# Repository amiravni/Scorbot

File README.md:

This is my work of building a Scorbot ER-V Controller with an arduino MEGA and drivers.

The project description is here: http://whatimade.today/geekcon-xii-scorbot-learns-to-draw/

Files and Folders consist of:

scorbotCOMcontrol - Most updated code, can get 6 encoder values and moves towards them

python - Python code for drawing images with scorbot

files - Some modified files to use with the python code

Eagle - Arduino mega shield design for scorbot

scorbotShieldTest - Shield Test...

Pins - Scorbot 50 Pins Data

ER3-Manual - Scorbot Manual

scorbotOldTestCode - My early work on scorbot, described here: http://www.whatimade.today/my-name-is-scorbot/

* Encoder_Scorbot - CPP code for encoders, taken and modified from  https://github.com/frodofski/Encoder_Polling_V2

* ScorbotCmd - The final code for controlling the Scorbot (Under Construction)

* ScorbotTest - Test code for Motors, Encoders and MicroSwitches

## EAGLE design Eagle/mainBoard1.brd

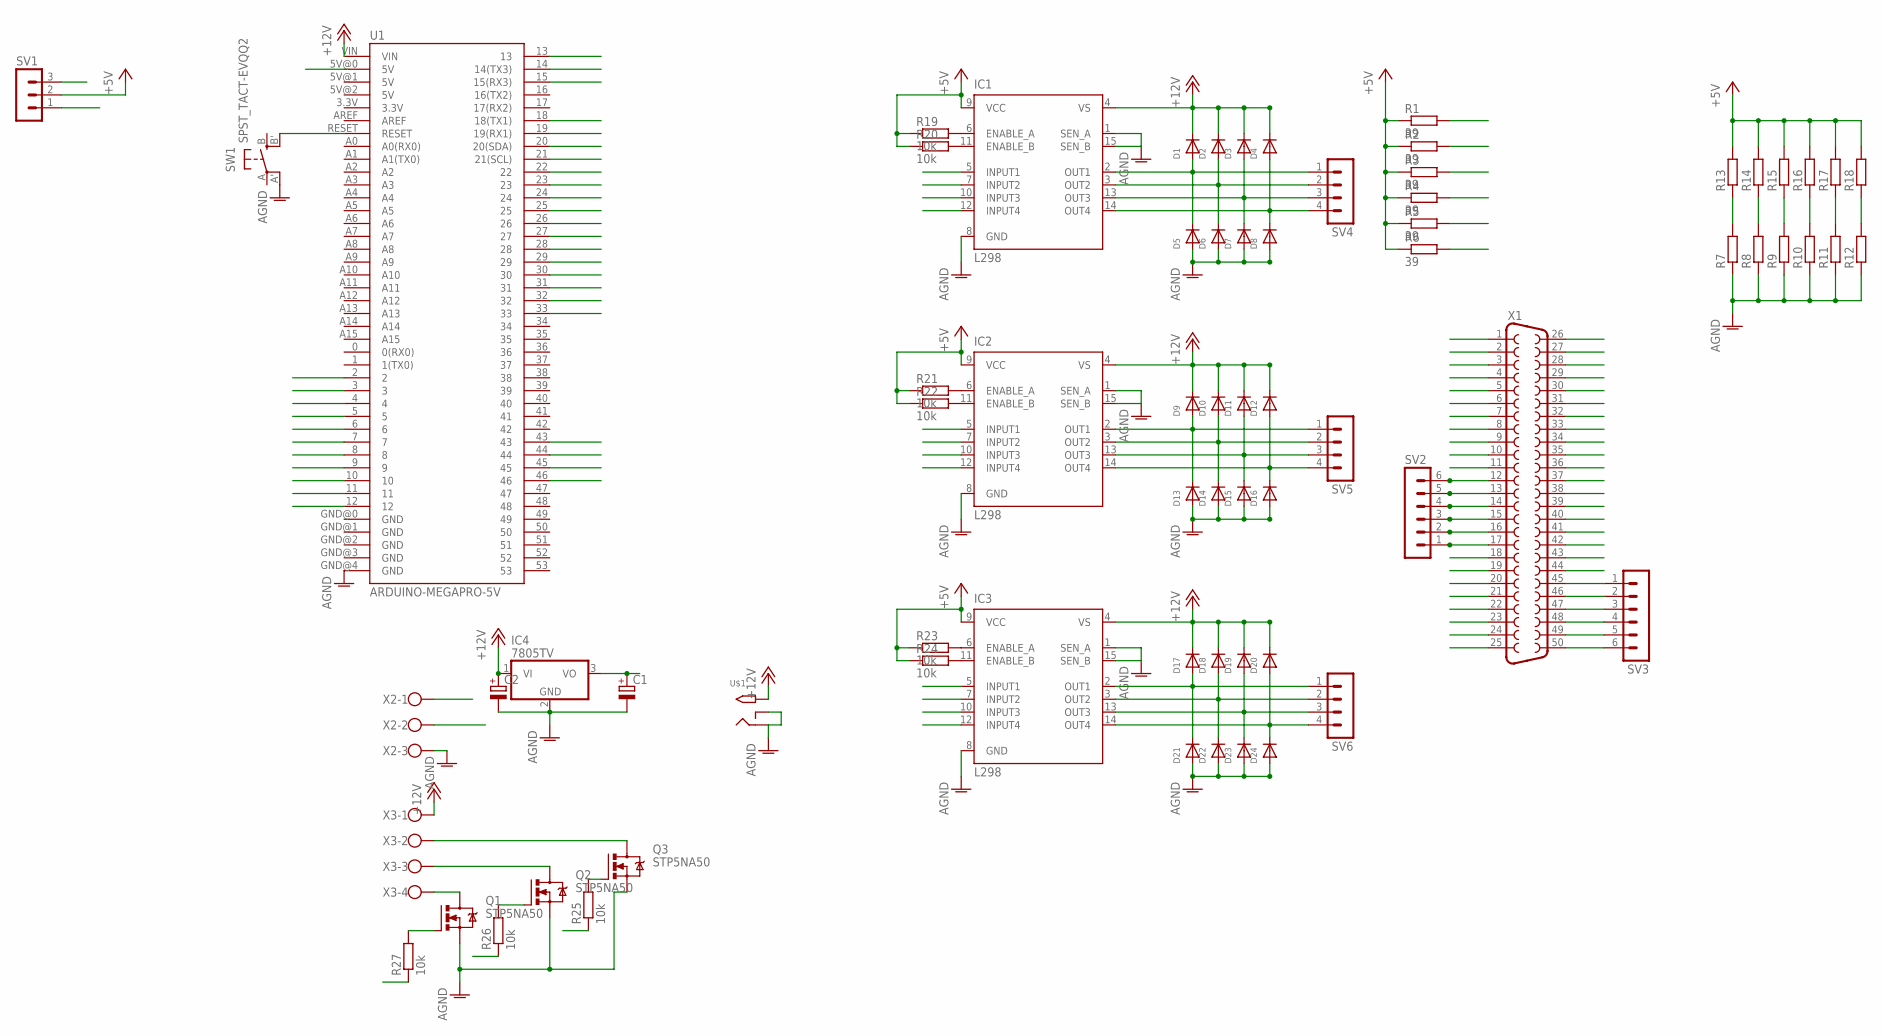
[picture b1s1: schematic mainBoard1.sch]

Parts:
C1, C2: CPOL-EUE2,5-6E; E2,5-6E
D1, D2, D3, D4, D5, D6, D7, D8, D9, D10, D11, D12, D13, D14, D15, D16, D17, D18, D19, D20, D21, D22, D23, D24: DIODESOD-323F; SOD-323F
IC1, IC2, IC3: L298; MULTIWATT-15
IC4: 7805TV; TO220V
Q1, Q2, Q3: STP5NA50; TO220BV
R1, R2, R3, R4, R5, R6: 39; 0207/10
R7, R8, R9, R10, R11, R12, R13, R14, R15, R16, R17, R18: R0207/10; 0207/10
R19, R20, R21, R22, R23, R24, R25, R26, R27: 10k; R0805
SV1: MA03-1
SV2, SV3: MA06-1
SV4, SV5, SV6: MA04-1
SW1: SPST_TACT-EVQQ2; EVQ-Q2
U1: ARDUINO-MEGAPRO-5V; ARDUINO_MEGA-PRO-5V
U$1: 2.1MMJACKTHM; PJ-102A
X1: F50VP
X2: W237-103
X3: W237-4

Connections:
5V_ARD: SV1.3, U1.5V@0 (5V)
5V_REG: C1.+, IC4.3 (VO), SV1.1, X2.1
+5V: IC1.9 (VCC), IC2.9 (VCC), IC3.9 (VCC), R1.1, R2.1, R3.1, R4.1, R5.1, R6.1, R13.2, R14.2, R15.2, R16.2, R17.2, R18.2, R19.1, R20.1, R21.1, R22.1, R23.1, R24.1, SV1.2
+12V: C2.+, D1.C, D2.C, D3.C, D4.C, D9.C, D10.C, D11.C, D12.C, D17.C, D18.C, D19.C, D20.C, IC1.4 (VS), IC2.4 (VS), IC3.4 (VS), IC4.1 (VI), U1.VIN, U$1.TIP, X3.1
AGND: C1.-, C2.-, D5.A, D6.A, D7.A, D8.A, D13.A, D14.A, D15.A, D16.A, D21.A, D22.A, D23.A, D24.A, IC1.1 (SEN_A), IC1.8 (GND), IC1.15 (SEN_B), IC2.1 (SEN_A), IC2.8 (GND), IC2.15 (SEN_B), IC3.1 (SEN_A), IC3.8 (GND), IC3.15 (SEN_B), IC4.2 (GND), Q1.S, Q2.S, Q3.S, R7.1, R8.1, R9.1, R10.1, R11.1, R12.1, SW1.A' (P1), U1.GND@4 (GND), U$1.RING, U$1.RING_SW, X1.28, X1.29, X1.30, X1.31, X1.32, X1.33, X2.3
LED_0: R1.2, X1.11
LED_1: R2.2, X1.27
LED_2: R3.2, X1.10
LED_3: R4.2, X1.26
LED_4: R5.2, X1.9
LED_5: R6.2, X1.25
LED_B: R27.1, U1.46
LED_DATA: U1.43, X2.2
LED_G: R26.1, U1.45
LED_R: R25.1, U1.44
M1_0: D1.A, D5.C, IC1.2 (OUT1), SV3.6, SV4.1, X1.50
M1_0_IN: IC1.5 (INPUT1), U1.14 (14(TX3))
M1_1: D3.A, D7.C, IC1.13 (OUT3), SV3.5, SV4.3, X1.49
M1_1_IN: IC1.10 (INPUT3), U1.4
M1_2: D9.A, D13.C, IC2.2 (OUT1), SV3.4, SV5.1, X1.48
M1_2_IN: IC2.5 (INPUT1), U1.6
M1_3: D11.A, D15.C, IC2.13 (OUT3), SV3.3, SV5.3, X1.47
M1_3_IN: IC2.10 (INPUT3), U1.8
M1_4: D17.A, D21.C, IC3.2 (OUT1), SV3.2, SV6.1, X1.46
M1_4_IN: IC3.5 (INPUT1), U1.10
M1_5: D19.A, D23.C, IC3.13 (OUT3), SV3.1, SV6.3, X1.45
M1_5_IN: IC3.10 (INPUT3), U1.12
M2_0: D2.A, D6.C, IC1.3 (OUT2), SV2.1, SV4.2, X1.17
M2_0_IN: IC1.7 (INPUT2), U1.15 (15(RX3))
M2_1: D4.A, D8.C, IC1.14 (OUT4), SV2.2, SV4.4, X1.16
M2_1_IN: IC1.12 (INPUT4), U1.5
M2_2: D10.A, D14.C, IC2.3 (OUT2), SV2.3, SV5.2, X1.15
M2_2_IN: IC2.7 (INPUT2), U1.7
M2_3: D12.A, D16.C, IC2.14 (OUT4), SV2.4, SV5.4, X1.14
M2_3_IN: IC2.12 (INPUT4), U1.9
M2_4: D18.A, D22.C, IC3.3 (OUT2), SV2.5, SV6.2, X1.13
M2_4_IN: IC3.7 (INPUT2), U1.11
M2_5: D20.A, D24.C, IC3.14 (OUT4), SV2.6, SV6.4, X1.12
M2_5_IN: IC3.12 (INPUT4), U1.13
MS_0: R7.2, R13.1, U1.2, X1.23
MS_1: R8.2, R14.1, U1.3, X1.7
MS_2: R9.2, R15.1, U1.21 (21(SCL)), X1.24
MS_3: R10.2, R16.1, U1.20 (20(SDA)), X1.8
MS_4: R11.2, R17.1, U1.19 (19(RX1)), X1.6
MS_5: R12.2, R18.1, U1.18 (18(TX1)), X1.22
unnamed: Q1.D, X3.4
unnamed: Q3.D, X3.2
unnamed: Q2.D, X3.3
unnamed: IC1.6 (ENABLE_A), R19.2
unnamed: IC1.11 (ENABLE_B), R20.2
unnamed: Q3.G, R25.2
unnamed: Q2.G, R26.2
unnamed: Q1.G, R27.2
unnamed: IC2.6 (ENABLE_A), R21.2
unnamed: IC2.11 (ENABLE_B), R22.2
unnamed: IC3.6 (ENABLE_A), R23.2
unnamed: IC3.11 (ENABLE_B), R24.2
unnamed: SW1.B' (S1), U1.RESET
P0_0: U1.22, X1.2
P0_1: U1.24, X1.1
P0_2: U1.26, X1.36
P0_3: U1.28, X1.35
P0_4: U1.30, X1.18
P0_5: U1.32, X1.34
P1_0: U1.23, X1.5
P1_1: U1.25, X1.21
P1_2: U1.27, X1.4
P1_3: U1.29, X1.20
P1_4: U1.31, X1.3
P1_5: U1.33, X1.19

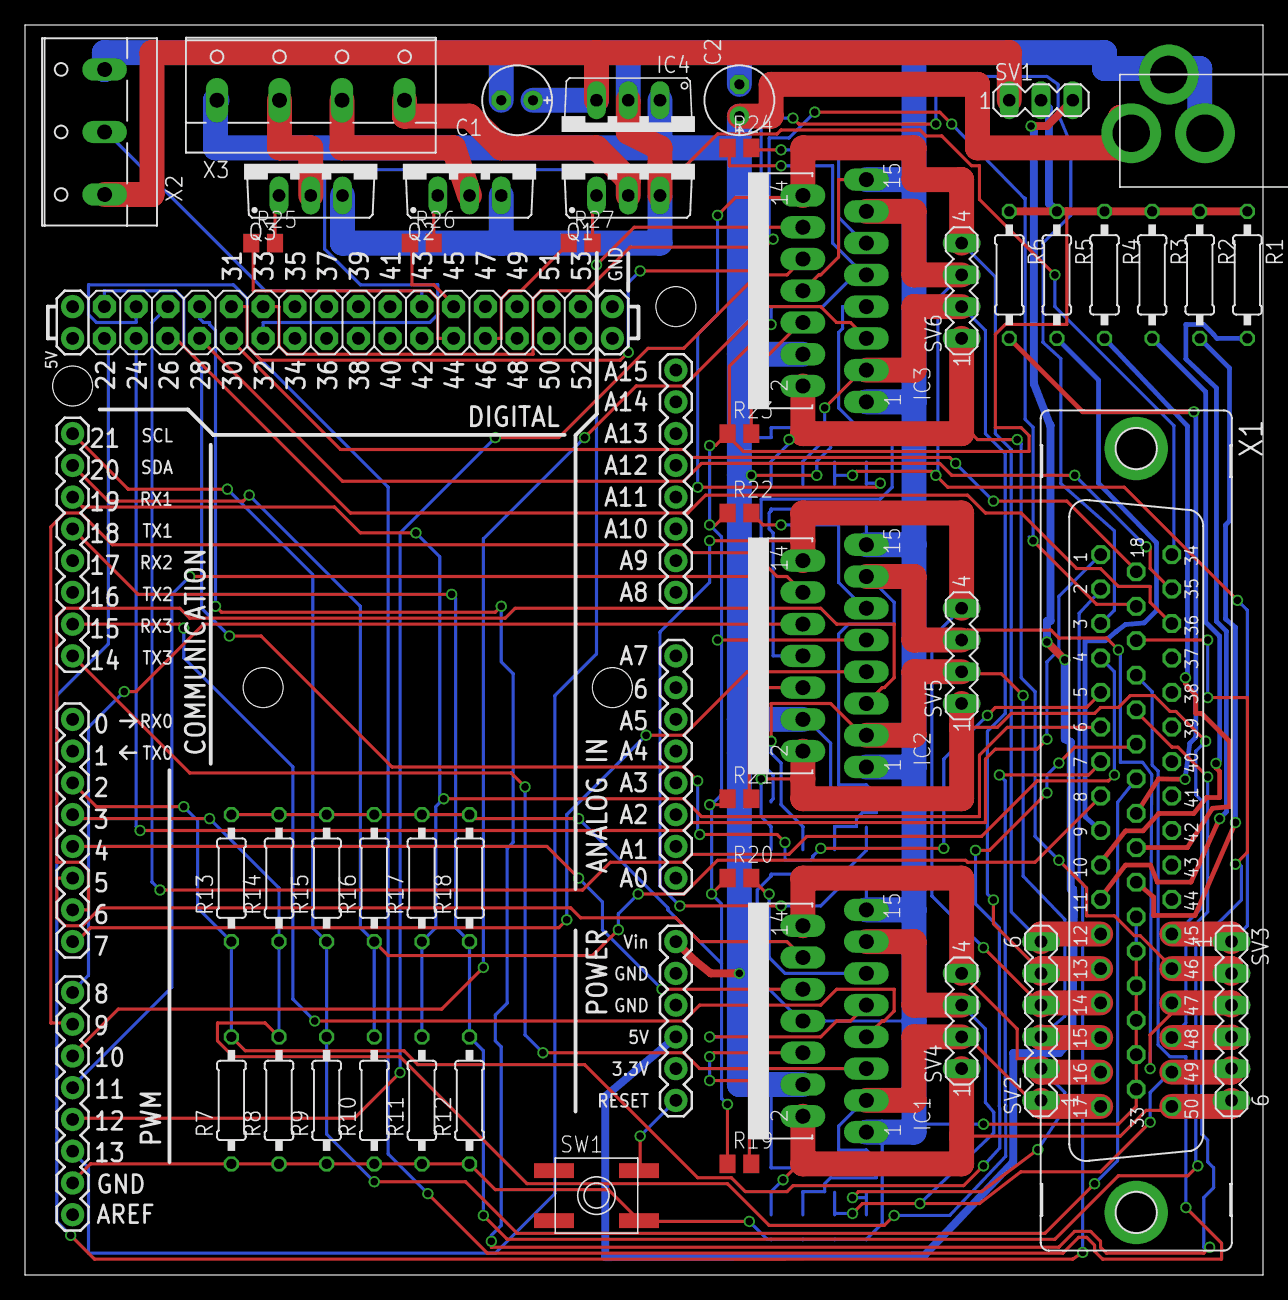
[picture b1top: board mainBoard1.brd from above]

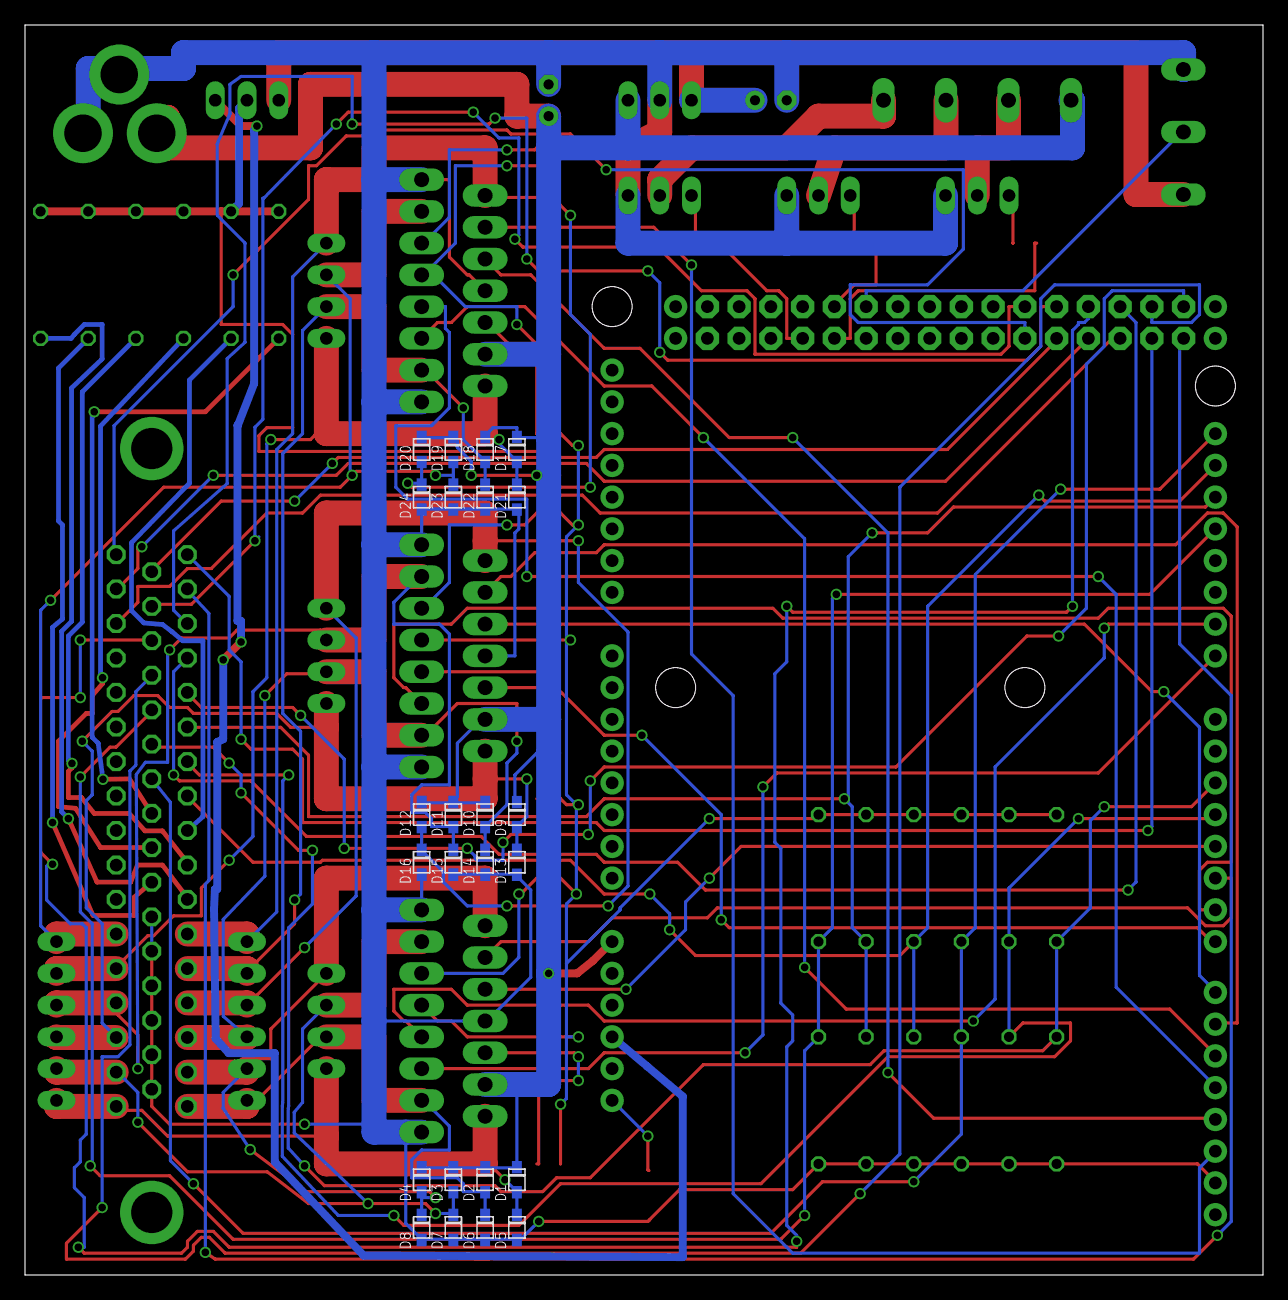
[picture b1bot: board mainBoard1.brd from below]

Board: 2 copper layers, 99.0 x 100.0 mm, 72 parts (24 on the bottom side), 70 nets.

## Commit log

2014-10-28 first
2014-10-29 DataSheet
2014-10-30 All encoder test
2014-10-30 All encoder Test + 1 MS
2014-10-31 TEST ready
2014-11-01 Menu + Go Home
2014-11-01 ReadMe
2014-11-15 Add Scorbot 1 arm control and FZZ
2016-09-26 Scorbot Geekcon Work
2016-09-26 Geekcon 12 project
2016-09-26 Rename ScorbotNewProtocolWithPoly.ino to ScorbotCOMcontrol.ino
2016-09-30 Added python files

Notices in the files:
parts and their libraries:
SparkFun-Boards: Licensing: Creative Commons ShareAlike 4.0 International - https://creativecommons.org/licenses/by-sa/4.0
